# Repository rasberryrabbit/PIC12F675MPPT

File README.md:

# PIC12F675MPPT
Solar MPPT circuit.  
  
This is simple MPPT for solar panel.  
New 3.2 firmware from 16F676 project.  
Test is ok as expected. ( jan 18 2019 )  
It's 50W limit design. Consider D6,D1,D2,L1 with more high power solar panel.  
  
11 mili-ohm N-ch logic level FET(BUK9511 or BUK9508) used for current sensor. 
It can replace by 11 mili-ohm or lower Rds-on resistance logic level FET.  
  
Transistor 2N2222A -> BC547 or compatible(reverse pin order)  
Transistor 2N2907A -> BC557 or compatible(reverse pin order)  
  
L1 100~330uH  
  
LM358N can replace by other pin-compatible regular OP-AMP. TLC272 is more works better.  
  
D8-D9 used for 3.6v Reference. Each has about 1.8v voltage drop.  
  
Q1 gate voltage is 3.6v. It's depend on FET specification.  
  
Q1, Q2 can skip heat spreader with low POWER Solar panel. No heat with 10W panel.  
  
(Note) Sometimes MPPT stalls no output. It caused by low FET bootstrap voltage.  
It's very rare condition. It may fixed by R9 change.

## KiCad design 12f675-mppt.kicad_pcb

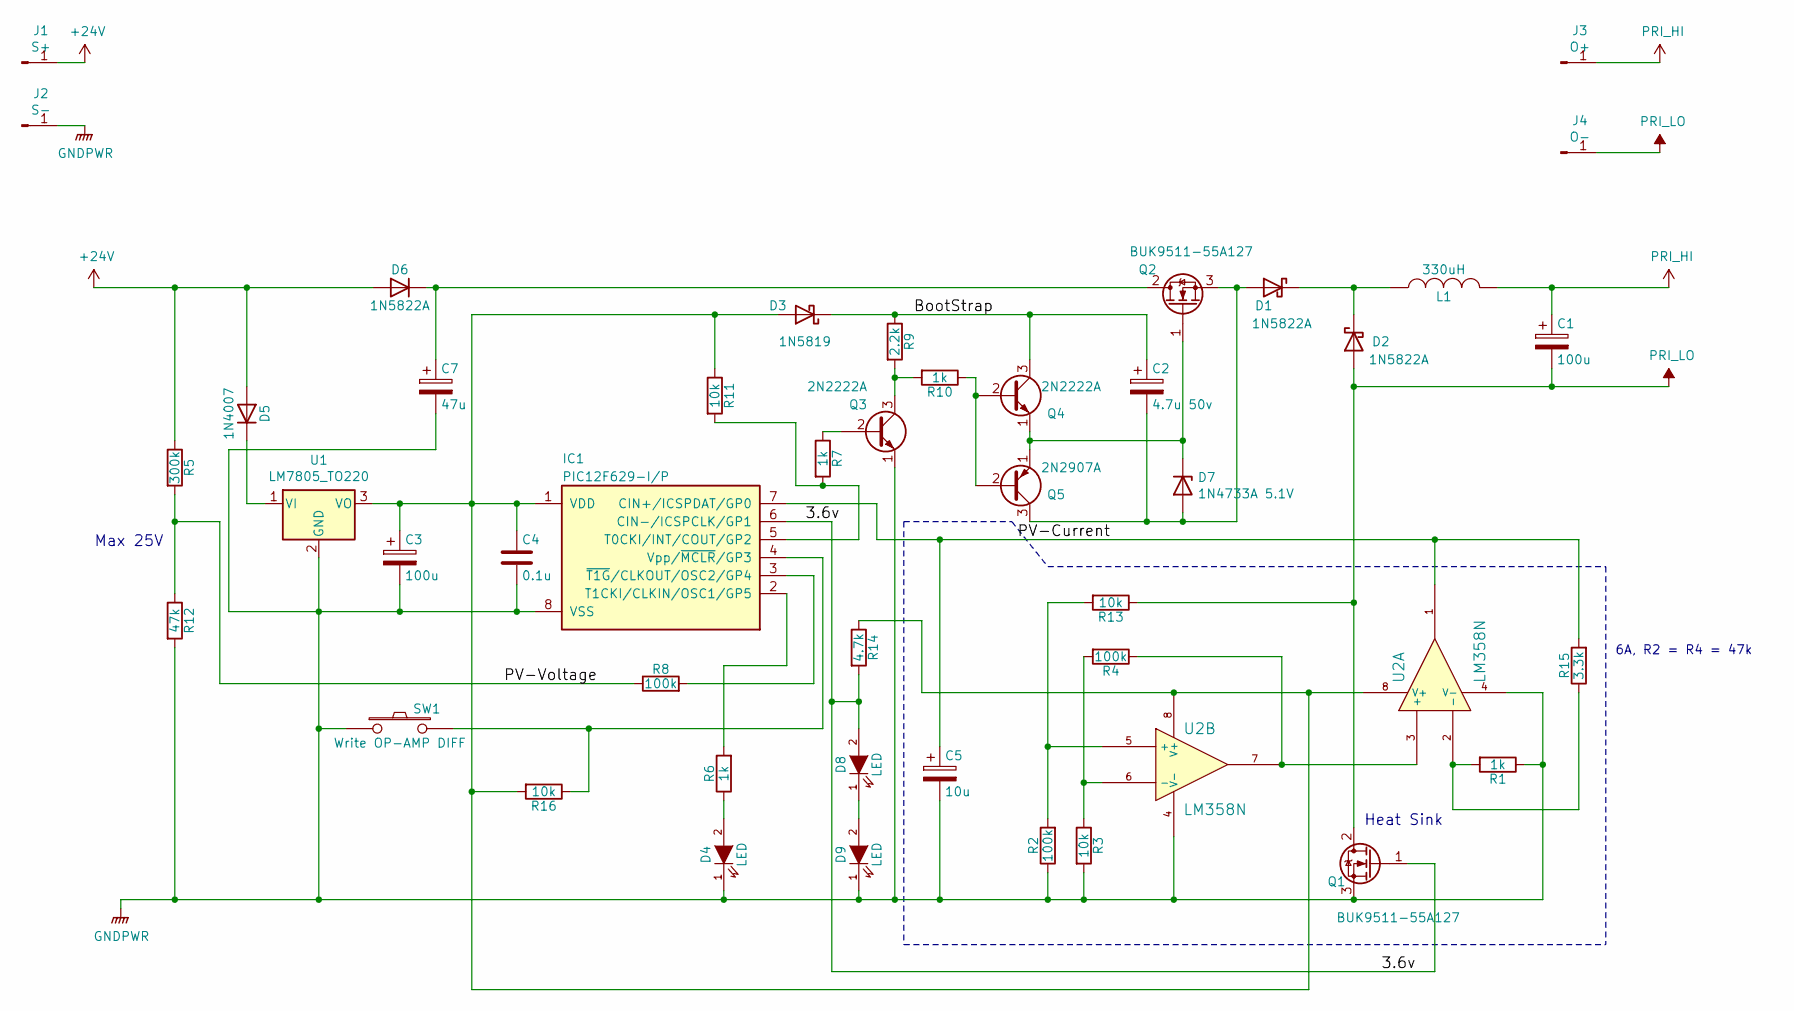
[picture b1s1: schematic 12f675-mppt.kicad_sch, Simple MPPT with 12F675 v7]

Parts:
C1, C3: 100u; CP_Radial_D12.5mm_P5.00mm
C2: 4.7u 50v; CP_Radial_D12.5mm_P5.00mm
C4: 0.1u; C_Disc_D7.5mm_W4.4mm_P5.00mm
C5: 10u; CP_Radial_D12.5mm_P5.00mm
C7: 47u; CP_Radial_D12.5mm_P5.00mm
D1, D2, D6: 1N5822A; D_DO-201AD_P15.24mm_Horizontal
D3: 1N5819; D_DO-41_SOD81_P10.16mm_Horizontal
D4, D8, D9: LED; LED_D4.0mm
D5: 1N4007; D_DO-41_SOD81_P10.16mm_Horizontal
D7: 1N4733A 5.1V; D_DO-41_SOD81_P10.16mm_Horizontal
IC1: PIC12F629-I/P; DIP-8_W7.62mm_LongPads
J1: S+; 1pin
J2: S-; 1pin
J3: O+; 1pin
J4: O-; 1pin
L1: 330uH; L_Toroid_Vertical_L33.0mm_W17.8mm_P12.70mm_Pulse_KM-5
Q1, Q2: BUK9511-55A127; TO-220-3_Vertical
Q3, Q4: 2N2222A; TO-92_Inline_Wide
Q5: 2N2907A; TO-92_Inline_Wide
R1, R6, R7, R10: 1k; R_Axial_DIN0309_L9.0mm_D3.2mm_P12.70mm_Horizontal
R2, R4, R8: 100k; R_Axial_DIN0309_L9.0mm_D3.2mm_P12.70mm_Horizontal
R3, R11, R13, R16: 10k; R_Axial_DIN0309_L9.0mm_D3.2mm_P12.70mm_Horizontal
R5: 300k; R_Axial_DIN0309_L9.0mm_D3.2mm_P12.70mm_Horizontal
R9: 2.2k; R_Axial_DIN0309_L9.0mm_D3.2mm_P12.70mm_Horizontal
R12: 47k; R_Axial_DIN0309_L9.0mm_D3.2mm_P12.70mm_Horizontal
R14: 4.7k; R_Axial_DIN0309_L9.0mm_D3.2mm_P12.70mm_Horizontal
R15: 3.3k; R_Axial_DIN0309_L9.0mm_D3.2mm_P12.70mm_Horizontal
SW1: Write OP-AMP DIFF; SW_PUSH_6mm
U1: LM7805_TO220; TO-220-3_Vertical
U2: LM358N; DIP-8_W7.62mm_LongPads

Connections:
+24V: D5.2 (A), D6.2 (A), J1.1, R5.1
/3.6v: D8.2 (A), IC1.6 (CIN-/ICSPCLK/GP1), Q1.1 (G), R14.2
/BootStrap: C2.1, D3.1 (K), Q4.3 (C), R9.1
/PV-Current: C5.1, IC1.7 (CIN+/ICSPDAT/GP0), R15.2, U2.1
/PV-Voltage: R5.2, R8.1, R12.1
GNDPWR: C3.2, C4.2, C5.2, C7.2, D4.1 (K), D9.1 (K), IC1.8 (VSS), J2.1, Q1.3 (S), Q3.1 (E), R1.1, R2.1, R3.2, R12.2, SW1.1, U1.2 (GND), U2.4 (V-)
unnamed: C2.2, D1.2 (A), D7.2 (A), Q2.3 (S), Q5.3 (C)
unnamed: D1.1 (K), D2.1 (K), L1.1
unnamed: C3.1, C4.1, D3.2 (A), IC1.1 (VDD), R11.1, R14.1, R16.2, U1.3 (VO), U2.8 (V+)
unnamed: D4.2 (A), R6.1
unnamed: D5.1 (K), U1.1 (VI)
unnamed: C7.1, D6.1 (K), Q2.2 (D)
unnamed: D7.1 (K), Q2.1 (G), Q4.1 (E), Q5.1 (E)
unnamed: D8.1 (K), D9.2 (A)
unnamed: IC1.5 (T0CKI/INT/COUT/GP2), R7.2, R11.2
unnamed: IC1.2 (T1CKI/CLKIN/OSC1/GP5), R6.2
unnamed: IC1.4 (Vpp/~MCLR/GP3), R16.1, SW1.2
unnamed: IC1.3 (~T1G/CLKOUT/OSC2/GP4), R8.2
unnamed: Q3.2 (B), R7.1
unnamed: Q3.3 (C), R9.2, R10.2
unnamed: Q4.2 (B), Q5.2 (B), R10.1
unnamed: R4.1, U2.3 (+), U2.7
unnamed: R1.2, R15.1, U2.2 (-)
unnamed: R2.2, R13.2, U2.5 (+)
unnamed: R3.1, R4.2, U2.6 (-)
PRI_HI: C1.1, J3.1, L1.2
PRI_LO: C1.2, D2.2 (A), J4.1, Q1.2 (D), R13.1

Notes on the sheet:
Max 25V
Heat Sink
6A, R2 = R4 = 47k

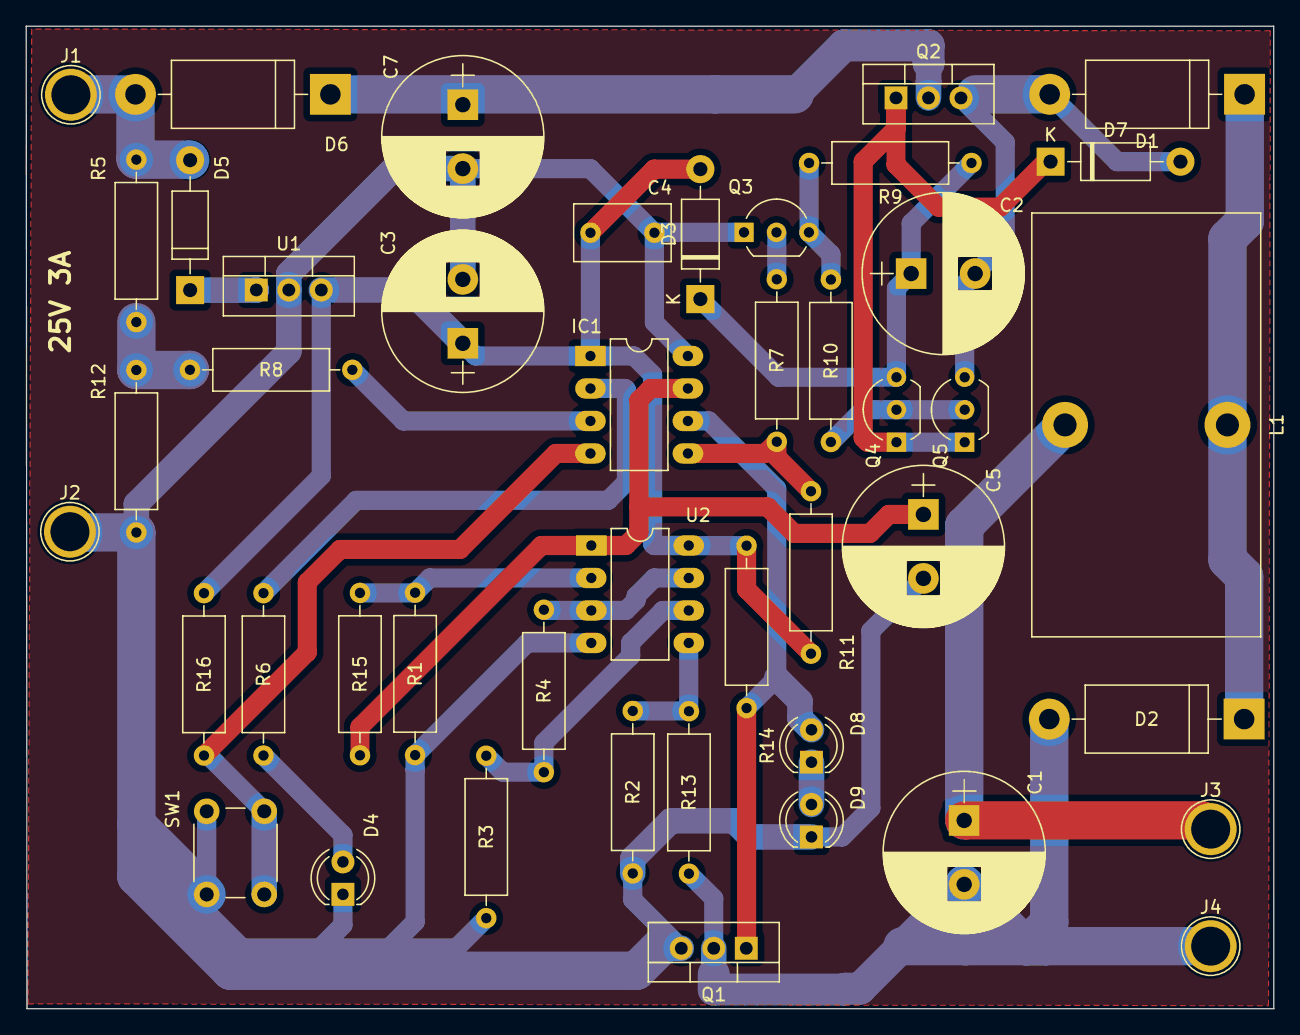
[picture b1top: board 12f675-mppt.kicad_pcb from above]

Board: 2 copper layers, 97.6 x 76.8 mm, 45 parts (0 on the bottom side), 27 nets.

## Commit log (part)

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2015-08-12 First commit.
2015-08-13 offset calibration does not work. Change to constant value. 2 is work for upto 14mV(pin 5) at no load. More accuracy read current value.
2015-08-13 More loop count on current check. lower offset current constant.
2015-08-13 Change Schematic. Use Reference voltage(pin 6). More Resistance on FET.
2015-08-14 More working on current sensing. Add 1uF capacitor to schematic.
2015-08-14 Change constant for testing at low current condition reset. It works ok on normal power supply.
2015-08-15 Update some parameters. Keep on testing.
2015-08-15 Correct current sensing.
2015-08-15 Remove current comparison.
2015-08-16 Fix circuit and code changes.
2015-08-18 Simple is the best. replace loop code for maximum power calibration. Change 100k to 200k ohm because current sensing voltage is too low.
2015-08-19 I forgot LM358 offset voltage error.
2015-08-20 Change ADC port reading order.
2015-08-22 Change low pass filter at ADC inputs. Narrows voltage range at solar panel.
2015-08-24 New code. Not fully tested.
2015-08-26 Reduce circuit parts. 3,6v to current sensing FET(low value on datasheet is 3v).
2015-08-30 Change ADC low pass filter's resisters(10k to 100k). New code.
2015-09-03 Remove Timer1 interrupt. More Switching frequency.
2015-09-06 More current, more power.
2015-09-06 Changing new method.
2015-09-07 Not perfect MPPT, but more power than direct connect.
2015-09-08 Change to new method again. focus on current.
2015-09-09 Some changes. It may works better.
2016-03-12 More duty on high load, but need more testing.
2016-03-13 Chnge parameter and more testing.
2016-03-13 More safe PWM-on value at low cell power.
2016-03-14 More stable output voltage.
2016-03-14 fix bug at adc values.
2016-03-14 Circuit design changes. more sensivity on current measuring adc.
2016-03-14 circuit v3. reduce op-amp amplification.
2016-03-16 refine codes, make better than direct connect. it work hopefully.
2016-03-17 New method on high power PWM scanning. It may work good and low ripple.
2016-03-18 Fix get life on useless code.
2016-03-18 Remove previous code. It really useless.
2016-03-18 More power output on high cell power condition. It need more testing.
2016-03-19 More testing.
2016-03-19 Add switch for OP-AMP calibration support. Push on this at no load and OP-AMP offset value write on eeprom.
2016-03-19 Forgot enabling compiler directive.
2016-04-15 Set zero at PWM Increasing value when Equal Power level And It read from eeprom. Testing.
2016-06-26 Fix average position on PWM. Finally, solar panel voltage is high on this fix. but make some voltage ripple.
2016-06-26 Reduce switching ripple by preventing zero voltage drop.
2016-06-27 Prevent big drop on PWM.
2016-06-28 Preventing slight drop on PWM. It is working good on osc checking. Vpp is about 8V on solar panel.
2016-07-05 Add 5min reset function but not enabled.
2016-07-06 Change PWM Limit divisor.
2016-07-06 Change hi PWM limit divisor.
2016-07-07 Correct division loss.
2016-07-09 Change optimal divisor for hi PWM. It may 4~8 and good with 6.
2016-07-09 More changes.
2016-07-09 back to old divisor value.
2016-07-10 Disable "Corr_Vol" and new Correcting avg PWM value.
2016-07-15 More stable output on some load.
2016-07-15 More stablize output.
2016-07-17 Revert some changes.
2016-07-17 Some changes.
2016-07-18 Changes.
2016-08-04 Remove useless code.
2016-08-05 New method.
2016-08-05 Update info.
2016-08-06 More power output. Maximum controled panel voltage to solar panel's adaptive output voltage and don't exceed much.
2018-06-07 fix type range error.
2018-07-15 make word size and delay 300ms on calibration.
2018-11-15 fix copy & paste errors.
2018-11-18 update capacitor and diode.
2018-11-18 reduce timer1 prescaler.
2018-11-30 Implement new method from 16f676 base project.
2018-11-30 Remove R11. It's a lot lower current sensing voltage.
2018-12-17 update code.
2018-12-17 Remove C6.
2019-01-11 Fix R2, R4 value. 300k -> 100k. Add R15 hint.
2019-01-11 update readme.
2019-01-11 Fix D6 value.
2019-01-18 test ok. no changes. fix readme comment.
2019-01-28 add PCB layout.
2019-01-31 Create LICENSE
2019-02-13 Enable BOD.
2019-02-13 Fix High-z turn on FET problem.
2019-02-13 update PCB.
2019-02-15 Change low PWM for boot strap charging.
2019-02-15 Fix R1, R15 values.
2019-02-16 Fix current sensing.
2019-02-24 Update current sensing resistors.
2019-05-05 Disable sync with PWM clock.
2019-05-06 Enable PWM checking.
2019-05-20 Change circuit. Exchange GP0(Current Sensing) and GP2(PWM).
2019-06-09 Remove low voltage protection code.
2021-04-17 Update comment.
2021-04-30 Add FET protection zener diode.
2021-05-02 Update PDF.
2021-05-07 R9 -> 2.2k
2021-05-08 Update.
2021-06-30 Set low PWM to 12.
2021-07-09 C2 to 4.7uF.
2021-07-30 Fix FET Bootstrap problem.
2021-07-30 Revert PWM_MIN.
2021-07-30 Revert and Change diode.
2021-08-01 Fix power comparison.
2021-08-02 Revert.
2022-01-14 Compiled by mikro Pascal 7.6.0
2025-11-25 Fix circuit. R1 -> 1k
2025-12-01 Update PCB files.
2025-12-01 Fix PWM.
2025-12-01 Remove some files.
2025-12-01 More PWM update.
